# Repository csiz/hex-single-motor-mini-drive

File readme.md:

Hex Mini FOC driver
===================

Brushless motor driver for mini gear motors and servos. This driver focuses on fine force control
using field oriented control (FOC). The motor can be commanded to move to track position, 
velocity, and/or force. The driver will maintain the current wave exactly 90 degrees out
of phase to the EMF wave for maximum efficieny. Position is tracked via hall sensors, EMF
feedback and I2C rotary sensors.

Electrical ranges: 
- Maximum motor voltage: 28V
- Maximum current: 5A
- Minimum motor voltage: 6V
- Nominal I2C voltage: 3.3V

This project has 4 main components, for details look at the `readme.md` files in each directory:
* A brushless motor simulator and motor principles explainer; under `motor-sim`.
* The driver PCB schematic and manufacturing files; under `circuits`.
* Custom driver firmware with Kalman filter position tracking and FOC driving logic; under `driver-code`.
* Driver control and monitoring webapp; also under `motor-sim`, the page titled `motor-monitor.md`.
* The interface spec and autogenerated serialization code under `interface`; because of this we
must use the `npm update --install-links` command when updating dependencies for `motor-sim`.
(TODO: this section needs updating to include the master circuit and master code and versioning and media and circuit libraries layout)

Screenshots
-----------

Motor monitor should look like this when connected to a motor: 

The motor sim, with GPU rendered soundwaves should look like this: 

Circuit Dev Log
---------------

Lessons learnt for driver code v0.4
-----------------------------------

[ ] VREF must be independent of the reference to the amplifier; and actually well insulated. The v0.2 and v0.3 are too noisy because of this I suspect.
[ ] Let's go back to USB with 5V and separate VCC power connector! Also allows us to drop the on-board buck converter and save space. Bonus for easy to
control from a computer/phone with any USB cable.

Tasks for v0.3
--------------

[v] Maybe switch to a oscillation damping gate resistor of 3ohm. The AO4266E switching parameter uses 
Rgen = 3ohm, I think this is their recommended gate resistance. Switched to 4.7ohm, closest basic resistor.

[v] Aaaargh!!! BOOT0 pin needs a pulldown resistor on the STM32G4!
[x] VREF+ should be tied to VDDA... VREF+ now has the capacitance required and drives the amplifier refrence too.

[v] Think about connectors better. We should either drop or double down on USB-C. It would be very user friendly and the power delivery 
allows us to pick the 9-24V we need, but might be cumbersombe to control 24 devices. The SPI bus with slim connectors let's us keep it 
tight and in-house. Would we want a cheap single-sided board with USB-C and also a compact double sided assembly without USB at all.
... Let's go for double sided compact without USB, with the better stm32g4 with 5 opamps (so we can also ditch the opamp).
[v] USB-C footprint was correct with the cutouts. What we have now is incorrect!

[v] Need master circuit.
[v] Need flexi rotation I2C sensors.
[v] Via diameter was too small, should be at least 0.2/0.45

Need to implement in v0.2
-------------------------

Features of current version:
[v] Measure power line voltage.
[x] Re-pick voltage boost capacitor and resistor pair (using P FETS).
[v] Re-pick gate oscillation damping resistor for the inputs to the power MOSFET.
[v] Crystal oscilator and pick matching caps.
[v] Power regulator.
[v] USB-C connector maybe?
[v] Debugging connection with the trace line.
[v] 4 half bridge outputs
[v] 4 voltage inputs for the 4 outputs
[v] 1 voltage input for VCC
[v] 2 (preferably 4) current inputs from the 4 outputs; I chose 4.
[x] maybe 1 current input for total current. It would leave us with a floating ground which is iffy.
[v] SPI connection to main board. Not ~I2C~, it's too slow and consumes too much current. SPI will need
a chip select pin, but allows for parallel devices. SPI has hardware CRC calculation, seems useful.
[v] Spare I2C connection for the magnetic sensors.
[v] Status LED.

Lessons from previous version:
[x] Measure gate turn on characteristics of existing circuit...
[x] Maybe switch to a oscillation damping gate resistor of 3ohm. The AO4266E switching parameter uses 
Rgen = 3ohm, I think this is their recommended gate resistance.
[x] Definitely need to think about daisy chaining these, maybe use a signal buffer/transciever with an enable pin,
and/or mosfet switch for the chip power on. I2C to master board is probably the best and easiest way.
[v] Oopsies I flipped the sign of the V phase current measurement lines.
[x] The boost gate should maybe be connected to the driver side of the shunt resistor. At the moment we're measuring current used to charge the high gate.
[x] There's a summing option for the current measurments. Try outputing U, V, U+V, U+V+W using the 4th spare output.
[v] ! Think carefully about the shunt resistor placement, there's big interference going on if we measure during high side. Timing it around ground as
common mode voltage seems to fix it. Is that the only way to measure all current going through the motor coils?
[v] ! Measure voltage of the motor coils!
[x] There's a conflict between i2c and timer 3 channel 2. Choose a different GPIO for the red LED.
	I2C1 and TIM3_CH2 remapped
	Description
	When the following conditions are met:
	• I2C1 and TIM3 are clocked.
	• I/O port pin PB5 is configured as an alternate function output
	there is a conflict between the TIM3_CH2 signal and the I2C1 SMBA signal (even if SMBA is not used).
	In these cases the I/O port pin PB5 is set to 1 by default if the I/O alternate function output is selected and I2C1 is
	clocked. TIM3_CH2 cannot be used in output mode.
	Workaround
	To avoid this conflict, TIM3_CH2 can only be used in input mode.

[x] Double sided board. Not just yet.
[x] Drop voltage regulator and rely on master board for 3.3V; filter it though. We just needed to look for better 
components, there are cheap and small options that work well for us.
[x] Look for thinner IDC connector, and definitely SMD version for easier routing, use of space behind connector.
[v] Add voltage probes for the phase connectors so we can measure voltage both during driving and open connections.
We need to measure driving voltage to make sure our MOSFETS are turned on and giving us the voltage we command!
[v] Use Kelvin sense resistors (or pad hack) for the current measurement to avoid the unknown solder resistance.
https://www.analog.com/media/en/analog-dialogue/volume-46/number-2/articles/optimize-high-current-sensing-accuracy.pdf
[v] Don't drop the hall sensors, yet!
[v] The big problem with our measurements occurs when we switch from continuous 0 output from the low mosfet to mixed
output with the high mosfet. Any amount of mixed output seems to add an offset to our current measurement. Might be
worth putting the current sense only on the low mosfet branch.
[x] Choose a different mosfet driver to lower the minimum voltage under 5V. The undervoltage protection must be there
for a reason. Anyway, we chose 6V and up.
[v] Make it work with steppers... Neat!

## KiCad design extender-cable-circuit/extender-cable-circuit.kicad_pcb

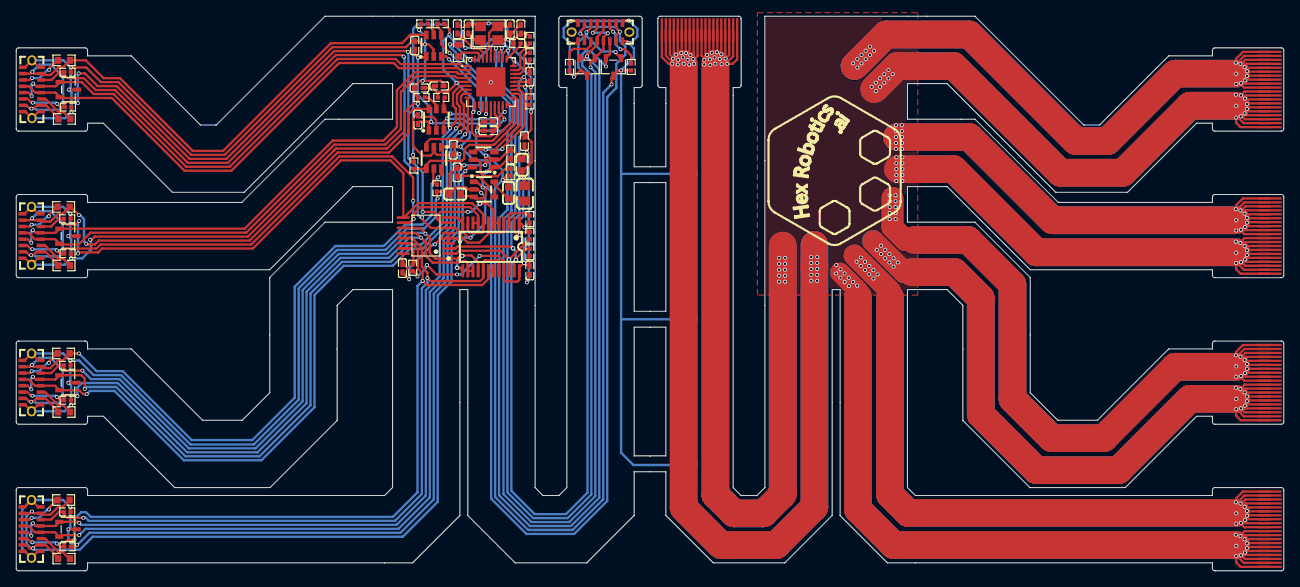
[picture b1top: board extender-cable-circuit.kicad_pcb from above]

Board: 2 copper layers, 160.0 x 70.0 mm, 80 parts (0 on the bottom side), 62 nets.

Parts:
C1, C2, C4, C5, C6, C7, C10, C11, C13, C14, C15, C16, C17, C18: 100nF; C0402
C8, C12, C20: 1uF; C0603
C19: 10nF; C0402
C72, C74: 15pF; C0402
D8, D10, D12, D14, D16, D18: SOT-23-3_L3.0-W1.7-P0.95-LS2.9-BR
FPC0, FPC1, FPC2, FPC3, FPC4: FPC-20P-P0.50-Pattern
L2: 10uH; L0805
R1, R2, R3, R4, R5, R8, R9: 10kΩ; R0402
R6, R7: 5.1kΩ; R0402
R17, R18, R19, R20, R76, R77, R78, R81: 56kΩ; R0603
R35, R55, R61, R66: 20kΩ; R0402
R54: 12kΩ; R0603
R79, R80, R82, R83: 100kΩ; R0402
R96, R97, R98, R99, R103, R104, R105, R106: 1MΩ; R0402
U1: TQFN-36_L6.0-W6.0-P0.50-BL-EP3.7
U3: SOT-23-5_L3.0-W1.6-P0.95-LS2.8-BL
U7, U23, U26, U28: SOT-23-6_L2.9-W1.6-P0.95-LS2.8-BR
U9: TSSOP-24_L7.8-W4.4-P0.65-LS6.4-BL
U14: TSSOP-16_L5.0-W4.4-P0.65-LS6.4-BL
USB0, USB1, USB2, USB3, USB4: USB-C-SMD_TC-005
X3: 24MHz; CRYSTAL-SMD_4P-L3.2-W2.5-BL

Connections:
3V3: C1.2, C2.2, C5.2, C6.2, C7.2, C10.2, C12.2, C13.2, C14.2, L2.2, R1.1, R2.2, R3.2, R4.1, R5.1, R8.1, R79.1, R80.1, R82.1, R83.1, U1.5 (VDDA33), U1.10 (VDDA33), U1.15 (VDD33), U1.23 (VDD33), U1.27 (VBUS_DET), U1.29 (VDDA33), U1.36 (VDDA33), U9.2 (A1), U9.21 (A2), U9.24 (VCC), U14.16 (VDD)
/3V3-before-filter: C8.2, L2.1, U3.5 (OUT)
/CC1: R6.2, USB0.A5 (CC1)
/CC2: R7.2, USB0.B5 (CC2)
/CFG_SEL1: R9.2, U1.25 (HS_IND/CFG_SEL1)
/LDO-Bypass-Capacitor: C19.2, U3.4 (BYP)
/NRESET: R5.2, U1.26 (RESET_N)
/PLLFILT: C4.2, U1.34 (PLLFILT)
/RBIAS: R54.1, U1.35 (RBIAS)
/XTAL1: C72.1, U1.33 (XTALIN/CLKIN), X3.1 (OSC1)
/XTAL2: C74.2, U1.32 (XTALOUT), X3.3 (OSC2)
/servo-usb-connector1/CC1x: R77.1, USB2.A5 (CC1)
/servo-usb-connector1/CC2x: R18.1, USB2.B5 (CC2)
/servo-usb-connector1/ILIMx: R55.2, U23.5 (ILIM)
/servo-usb-connector1/VBUSx: R18.2, R77.2, U23.6 (OUT), USB2.A4 (VBUS), USB2.A9 (VBUS), USB2.B4 (VBUS), USB2.B9 (VBUS)
/servo-usb-connector2/CC1x: R78.1, USB3.A5 (CC1)
/servo-usb-connector2/CC2x: R19.1, USB3.B5 (CC2)
/servo-usb-connector2/ILIMx: R61.2, U26.5 (ILIM)
/servo-usb-connector2/VBUSx: R19.2, R78.2, U26.6 (OUT), USB3.A4 (VBUS), USB3.A9 (VBUS), USB3.B4 (VBUS), USB3.B9 (VBUS)
/servo-usb-connector3/CC1x: R81.1, USB4.A5 (CC1)
/servo-usb-connector3/CC2x: R20.1, USB4.B5 (CC2)
/servo-usb-connector3/ILIMx: R66.2, U28.5 (ILIM)
/servo-usb-connector3/VBUSx: R20.2, R81.2, U28.6 (OUT), USB4.A4 (VBUS), USB4.A9 (VBUS), USB4.B4 (VBUS), USB4.B9 (VBUS)
/servo-usb-connector/CC1x: R76.1, USB1.A5 (CC1)
/servo-usb-connector/CC2x: R17.1, USB1.B5 (CC2)
/servo-usb-connector/ILIMx: R35.2, U7.5 (ILIM)
/servo-usb-connector/VBUSx: R17.2, R76.2, U7.6 (OUT), USB1.A4 (VBUS), USB1.A9 (VBUS), USB1.B4 (VBUS), USB1.B9 (VBUS)
GND: C1.1, C2.1, C4.1, C5.1, C6.1, C7.1, C8.1, C10.1, C11.1, C12.1, C13.1, C14.1, C15.1, C16.1, C17.1, C18.1, C19.1, C20.1, C72.2, C74.1, D8.3 (K), D10.3 (K), D12.3 (K), D14.3 (K), D16.3 (K), D18.3 (K), FPC0.1, FPC0.2, FPC0.3, FPC0.4, FPC0.5, FPC0.6, FPC0.7, FPC0.8, FPC0.9, FPC0.10, FPC1.1, FPC1.2, FPC1.3, FPC1.4, FPC1.5, FPC1.6, FPC1.7, FPC1.8, FPC1.9, FPC1.10, FPC2.1, FPC2.2, FPC2.3, FPC2.4, FPC2.5, FPC2.6, FPC2.7, FPC2.8, FPC2.9, FPC2.10, FPC3.1, FPC3.2, FPC3.3, FPC3.4, FPC3.5, FPC3.6, FPC3.7, FPC3.8, FPC3.9, FPC3.10, FPC4.1, FPC4.2, FPC4.3, FPC4.4, FPC4.5, FPC4.6, FPC4.7, FPC4.8, FPC4.9, FPC4.10, R6.1, R7.1, R9.1, R35.1, R54.2, R55.1, R61.1, R66.1, R96.1, R97.1, R98.1, R99.1, R103.1, R104.1, R105.1, R106.1, U1.37 (EP), U3.2 (GND), U7.2 (GND), U9.1 (A0), U9.12 (GND), U14.3 (A0), U14.4 (A1), U14.5 (A2), U14.8 (VSS), U23.2 (GND), U26.2 (GND), U28.2 (GND), USB0.A1 (GND), USB0.A12 (GND), USB0.B1 (GND), USB0.B12 (GND), USB1.1 (EH), USB1.2 (EH), USB1.A1 (GND), USB1.A12 (GND), USB1.B1 (GND), USB1.B12 (GND), USB2.1 (EH), USB2.2 (EH), USB2.A1 (GND), USB2.A12 (GND), USB2.B1 (GND), USB2.B12 (GND), USB3.1 (EH), USB3.2 (EH), USB3.A1 (GND), USB3.A12 (GND), USB3.B1 (GND), USB3.B12 (GND), USB4.1 (EH), USB4.2 (EH), USB4.A1 (GND), USB4.A12 (GND), USB4.B1 (GND), USB4.B12 (GND), X3.2 (GND), X3.4 (GND)
I2C_SCL: D10.2 (A1), R2.1, U1.24 (SCL/SMBCLK/CFG_SEL0), U9.22 (SCL), U14.1 (SCL), USB0.A8 (SUB1)
I2C_SDA: D10.1 (A1), R3.1, U1.22 (SDA/SMBBATA/NON_REM1), U9.23 (SDA), U14.2 (SDA), USB0.B8 (SUB2)
IN_USB_D+: D8.2 (A1), U1.31 (USBDP_UP), USB0.A6 (DP1), USB0.B6 (DP2)
IN_USB_D-: D8.1 (A1), U1.30 (USBDM_UP), USB0.A7 (DN1), USB0.B7 (DN2)
unnamed: C11.2, U1.14 (CRFILT)
unnamed: R8.2, U1.28 (SUSP_IND/LOCAL_PWR/NON_REM0)
unnamed: R1.2, U9.3 (RESET#)
unnamed: R4.2, U14.15 (RESET#)
PRTPWR1: U1.12 (PRTPWR1/BC_EN1), U7.3 (EN)
PRTPWR2: U1.16 (PRTPWR2/BC_EN2), U23.3 (EN)
PRTPWR3: U1.18 (PRTPWR3/BC_EN3), U26.3 (EN)
PRTPWR4: U1.20 (PRTPWR4/BC_EN4), U28.3 (EN)
SERVO1_BOOT0: R96.2, U9.4 (SD0), U9.7 (SC1), U14.6 (IO0), USB1.A8 (SUB1)
SERVO1_NRST: R103.2, U9.5 (SC0), U9.6 (SD1), U14.7 (IO1), USB1.B8 (SUB2)
SERVO2_BOOT0: R97.2, U9.8 (SD2), U9.11 (SC3), U14.9 (IO2), USB2.A8 (SUB1)
SERVO2_NRST: R104.2, U9.9 (SC2), U9.10 (SD3), U14.10 (IO3), USB2.B8 (SUB2)
SERVO3_BOOT0: R98.2, U9.13 (SD4), U9.16 (SC5), U14.11 (IO4), USB3.A8 (SUB1)
SERVO3_NRST: R105.2, U9.14 (SC4), U9.15 (SD5), U14.12 (IO5), USB3.B8 (SUB2)
SERVO4_BOOT0: R99.2, U9.17 (SD6), U9.20 (SC7), U14.13 (IO6), USB4.A8 (SUB1)
SERVO4_NRST: R106.2, U9.18 (SC6), U9.19 (SD7), U14.14 (IO7), USB4.B8 (SUB2)
USBDN1_D+: D12.2 (A1), U1.2 (USBDP_DN1/PRT_DIS_P1), USB1.A6 (DP1), USB1.B6 (DP2)
USBDN1_D-: D12.1 (A1), U1.1 (USBDM_DN1/PRT_DIS_M1), USB1.A7 (DN1), USB1.B7 (DN2)
USBDN2_D+: D14.2 (A1), U1.4 (USBDP_DN2/PRT_DIS_P2), USB2.A6 (DP1), USB2.B6 (DP2)
USBDN2_D-: D14.1 (A1), U1.3 (USBDM_DN2/PRT_DIS_M2), USB2.A7 (DN1), USB2.B7 (DN2)
USBDN3_D+: D16.2 (A1), U1.7 (USBDP_DN3/PRT_DIS_P3), USB3.A6 (DP1), USB3.B6 (DP2)
USBDN3_D-: D16.1 (A1), U1.6 (USBDM_DN3/PRT_DIS_M3), USB3.A7 (DN1), USB3.B7 (DN2)
USBDN4_D+: D18.2 (A1), U1.9 (USBDP_DN4/PRT_DIS_P4), USB4.A6 (DP1), USB4.B6 (DP2)
USBDN4_D-: D18.1 (A1), U1.8 (USBDM_DN4/PRT_DIS_M4), USB4.A7 (DN1), USB4.B7 (DN2)
VBUS: C15.2, C16.2, C17.2, C18.2, C20.2, U3.1 (IN), U3.3 (EN), U7.1 (IN), U23.1 (IN), U26.1 (IN), U28.1 (IN), USB0.A4 (VBUS), USB0.A9 (VBUS), USB0.B4 (VBUS), USB0.B9 (VBUS)
VCC: FPC0.11, FPC0.12, FPC0.13, FPC0.14, FPC0.15, FPC0.16, FPC0.17, FPC0.18, FPC0.19, FPC0.20, FPC1.11, FPC1.12, FPC1.13, FPC1.14, FPC1.15, FPC1.16, FPC1.17, FPC1.18, FPC1.19, FPC1.20, FPC2.11, FPC2.12, FPC2.13, FPC2.14, FPC2.15, FPC2.16, FPC2.17, FPC2.18, FPC2.19, FPC2.20, FPC3.11, FPC3.12, FPC3.13, FPC3.14, FPC3.15, FPC3.16, FPC3.17, FPC3.18, FPC3.19, FPC3.20, FPC4.11, FPC4.12, FPC4.13, FPC4.14, FPC4.15, FPC4.16, FPC4.17, FPC4.18, FPC4.19, FPC4.20
nOCS1: R79.2, U1.13 (OCS_N1), U7.4 (/FAULT)
nOCS2: R80.2, U1.17 (OCS_N2), U23.4 (/FAULT)
nOCS3: R82.2, U1.19 (OCS_N3), U26.4 (/FAULT)
nOCS4: R83.2, U1.21 (OCS_N4), U28.4 (/FAULT)

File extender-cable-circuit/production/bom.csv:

Designator,Footprint,Quantity,Value,LCSC Part #
"C1, C10, C11, C13, C14, C15, C16, C17, C18, C2, C4, C5, C6, C7",C0402,14,100nF,C60474
"C12, C20, C8",C0603,3,1uF,C15849
C19,C0402,1,10nF,C15195
"C72, C74",C0402,2,15pF,C1548
"D10, D12, D14, D16, D18, D8",SOT-23-3_L3.0-W1.7-P0.95-LS2.9-BR,6,~,C32677
L2,L0805,1,10uH,C1046
"R1, R2, R3, R4, R5, R8, R9",R0402,7,10kΩ,C25744
"R103, R104, R105, R106, R96, R97, R98, R99",R0402,8,1MΩ,C26083
"R17, R18, R19, R20, R76, R77, R78, R81",R0603,8,56kΩ,C23206
"R35, R55, R61, R66",R0402,4,20kΩ,C25765
R54,R0603,1,12kΩ,C22790
"R6, R7",R0402,2,5.1kΩ,C25905
"R79, R80, R82, R83",R0402,4,100kΩ,C25741
U1,TQFN-36_L6.0-W6.0-P0.50-BL-EP3.7,1,~,C58940
U14,TSSOP-16_L5.0-W4.4-P0.65-LS6.4-BL,1,~,C141380
"U23, U26, U28, U7",SOT-23-6_L2.9-W1.6-P0.95-LS2.8-BR,4,~,C55266
U3,SOT-23-5_L3.0-W1.6-P0.95-LS2.8-BL,1,~,C2969807
U9,TSSOP-24_L7.8-W4.4-P0.65-LS6.4-BL,1,~,C130026
"USB0, USB1, USB2, USB3, USB4",USB-C-SMD_TC-005,5,~,C6332285
X3,CRYSTAL-SMD_4P-L3.2-W2.5-BL,1,24MHz,C15643

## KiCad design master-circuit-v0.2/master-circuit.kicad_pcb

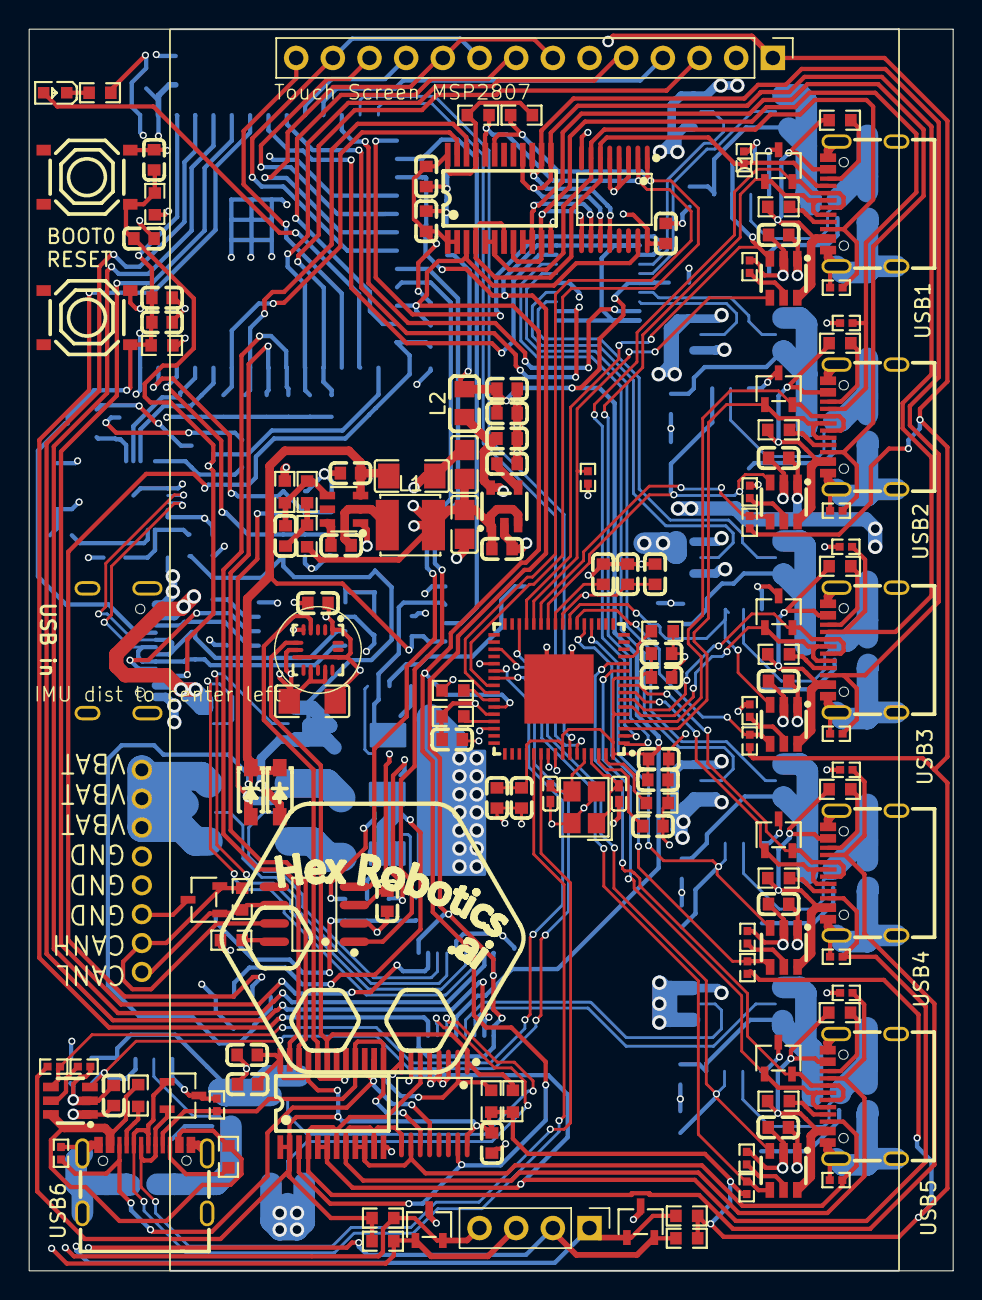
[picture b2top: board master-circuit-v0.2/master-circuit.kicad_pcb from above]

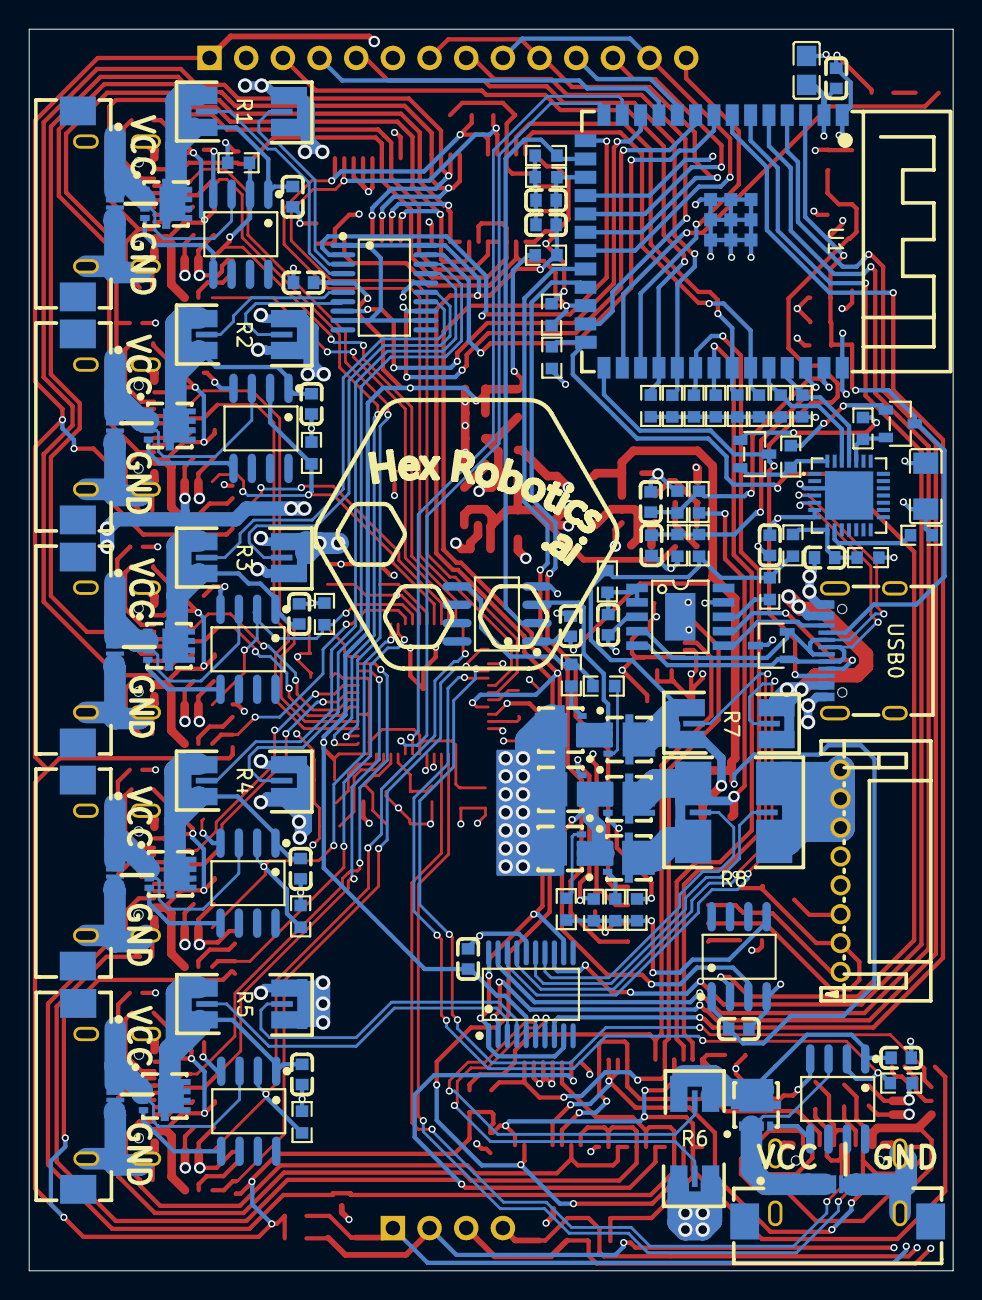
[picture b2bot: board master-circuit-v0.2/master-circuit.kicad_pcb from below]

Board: 4 copper layers, 64.0 x 86.0 mm, 238 parts (100 on the bottom side), 184 nets.

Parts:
C1, C8, C12, C15, C18, C20, C25, C26, C27, C28, C29, C33, C35, C40, C51, C52, C53, C54, C55, C56, C57, C58, C59, C63, C65, C71, C84, C85: 1uF; C0603
C2, C4, C5, C7, C13, C16, C22, C30, C31, C34, C38, C39, C42, C43, C44, C45, C60, C61, C62, C66, C67, C68, C70: 100nF; C0603
C3, C23, C24: 22uF; C0805
C6: 100pF; C0603
C9: 10nF; C0603
C10, C11: 1nF; C0603
C17, C21, C32: 10uF; C1206
C64, C69: 15pF; C0402
D1, D2, D4, D5, D6, D7, D8, D9, D10, D11: SOT-23-3_L3.0-W1.7-P0.95-LS2.9-BR
D12, D14: SOD-123_L2.7-W1.6-LS3.7-RD-1
FPC1, FPC2, FPC3, FPC4, FPC5, FPC6: FPC-SMD_20P-P0.50_XUNPU_FPC-05F-20PH20
L1: 15uH; IND-SMD_L4.0-W4.0
L2: 10uH; L0805
LED1: LED0603-RD
Q8, Q12, Q14, Q16, Q18, Q20, Q21, Q22, Q23, Q24, Q25, Q26: WDFN-5_L3.1-W3.1-P0.65-BL_1
Q9, Q10: SOT-23-3_L2.9-W1.3-P1.90-LS2.4-BR
R1, R2, R3, R4, R5, R6, R7: 5mΩ; R2512 Shunt with Kelvin connections
R8: 1mΩ; R2725 Shunt with Kelvin connections
R9, R11, R12, R14, R15, R17, R18, R21, R22, R24, R25, R26, R27, R29, R30, R31, R32, R33, R34, R37, R38, R42, R43, R44, R47, R51, R52, R53, R58, R60, R64, R72, R73, R74, R78, R95, R102, R109: 10kΩ; R0603
R10: 49.9Ω; R0603
R13, R28, R46, R59, R65, R71, R76, R85, R86, R87, R88, R89: 56kΩ; R0603
R16: 120Ω; R0603
R23, R39: 1.5kΩ; R0603
R35, R55, R61, R66, R67, R70: 20kΩ; R0402
R40: 20kΩ; R0603
R41: 47kΩ; R0603
R45, R48, R56: 100kΩ; R0603
R50: 12kΩ; R0603
R62: 13kΩ; R0603
R68: 1kΩ; R0603
R77, R81, R90, R92, R93, R94: 4.7Ω; R0603
R79, R80, R82, R83, R84, R91: 100kΩ; R0402
R96, R97, R98, R99, R100, R101, R103, R104, R105, R106, R107, R108: 1MΩ; R0402
SW1, SW2: SW-SMD_4P-L5.1-W5.1-P3.70-LS6.5-TL_H1.5
U1: WIRELM-SMD_ESP32-S3-WROOM-1
U3: SOT-23-5_L3.0-W1.6-P0.95-LS2.8-BL
U4: SOT-23-6_L2.9-W1.6-P0.95-LS2.8-BL
U7, U23, U26, U28, U30, U32: SOT-23-6_L2.9-W1.6-P0.95-LS2.8-BR
U9, U13: TSSOP-24_L7.8-W4.4-P0.65-LS6.4-BL
U10: QFN-28_L5.0-W5.0-P0.50-TL-EP3.3
U11, U16: TSSOP-20_L6.5-W4.4-P0.65-LS6.4-BL
U14, U15: TSSOP-16_L5.0-W4.4-P0.65-LS6.4-BL
U17, U41, U43, U44, U45, U46, U47, U48, U49: SOIC-8_L4.9-W3.9-P1.27-LS6.0-BL
U18: LGA-16_L3.0-W3.0-P0.50-TL
U19: CONN-TH_S8B-PH-K-S-LF-SN
U24: QFN-64_L9.0-W9.0-P0.50-BL-EP4.8
U35: MSP2807 OLED with touchescreen and SD card
U42: ESSOP-10_L4.9-W3.9-P1.0-LS6.0-TL-EP
USB0, USB1, USB2, USB3, USB4, USB5, USB6: USB-C-SMD_TYPE-C16PIN
X2: 24MHz; CRYSTAL-SMD_4P-L3.2-W2.5-BL

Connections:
3V3: C2.2, C3.2, C8.2, C16.2, C17.2, C30.2, C31.2, C32.2, C42.2, C43.2, C44.2, C45.2, C59.2, C60.2, C68.2, C84.2, C85.2, L2.1, R9.2, R14.2, R15.2, R17.2, R18.2, R24.2, R25.2, R26.2, R27.2, R29.2, R32.2, R33.2, R34.2, R37.2, R39.1, R42.1, R51.2, R53.2, R58.2, R60.2, R64.2, R79.1, R80.1, R82.1, R83.1, R84.1, R91.1, U1.2 (3V3), U3.5 (OUT), U9.1 (A0), U9.2 (A1), U9.21 (A2), U9.24 (VCC), U10.6 (VDD), U10.7 (VREGIN), U13.1 (A0), U13.2 (A1), U13.21 (A2), U13.24 (VCC), U14.16 (VDD), U15.16 (VDD), U17.3 (VCC), U18.1 (VDD_IO), U18.8 (CS), U18.14 (VDD), U24.24 (VDD33CR), U24.37 (OCS7_N), U24.44 (VBUS_DET), U24.46 (VDD33), U35.1 (VCC)
3V3A: C12.2, C13.2, C38.2, C39.2, C61.2, C62.2, C66.2, C67.2, C70.2, C71.2, L2.2, R21.2, U11.5 (VS), U16.5 (VS), U24.5 (VDDA33), U24.10 (VDDA33), U24.52 (VDDA33), U24.57 (VDDA33), U24.64 (VDD33PLL)
5V: C15.2, C20.2, C23.2, C24.2, C26.2, C27.2, C28.2, C33.2, C40.2, L1.2, R10.2, U3.1 (IN), U3.3 (EN), U7.1 (IN), U23.1 (IN), U26.1 (IN), U28.1 (IN), U30.1 (IN), U32.1 (IN)
+Probe-1: R1.4 (Probe-2), U11.3 (IN±1)
+Probe-2: R2.4 (Probe-2), U11.7 (IN±2)
+Probe-3: R3.4 (Probe-2), U11.15 (IN+3)
+Probe-4: R4.4 (Probe-2), U11.18 (IN±4)
+Probe-5: R5.4 (Probe-2), U16.4 (IN+1)
+Probe-6: R6.4 (Probe-2), U16.7 (IN±2)
+Probe-7: R7.4 (Probe-2), U16.17 (IN+4)
+Probe-8: R8.4 (Probe-2), U16.14 (IN±3)
-Probe-1: R1.3 (Probe-1), U11.4 (IN+1)
-Probe-2: R2.3 (Probe-1), U11.6 (IN+2)
-Probe-3: R3.3 (Probe-1), U11.14 (IN±3)
-Probe-4: R4.3 (Probe-1), U11.17 (IN+4)
-Probe-5: R5.3 (Probe-1), U16.3 (IN±1)
-Probe-6: R6.3 (Probe-1), U16.6 (IN+2)
-Probe-7: R7.3 (Probe-1), U16.18 (IN±4)
-Probe-8: R8.3 (Probe-1), U16.15 (IN+3)
/Buck-Bootstrap-Capacitor: C7.1, U4.6 (BOOT)
/Buck-Output-SW: C7.2, L1.1, U4.2 (SW)
/Buck-Probe-Point: C6.2, R10.1, R56.2
/CAN-RS-SLOPE_CONTROL: R31.2, U17.8 (RS)
/CFG_SEL1: R52.2, U24.42 (HS_IND/CFG_SEL1)
/CFG_SEL2: R30.2, U24.13 (CFG_SEL2)
/DTR-GATE: Q9.1 (B), R43.1
/Gate1-vbattery: Q18.4 (G), R90.2
/Gate1-vbus: Q14.4 (G), R81.2
/Gate2-vbattery: Q20.4 (G), R92.2
/Gate2-vbus: Q16.4 (G), R77.2
/Gate3-vbattery: Q21.4 (G), R93.2
/Gate4-vbattery: Q22.4 (G), R94.2
/LDO-Bypass-Capacitor: C9.2, U3.4 (BYP)
/PD-VBUS-DETECT: R72.2, U42.8 (VBUS)
/PD-VDD: C29.2, R68.2, U42.1 (VDD), U42.2 (CFG2)
/RBIAS: R50.1, U24.63 (RBIAS)
/RTS-GATE: Q10.1 (B), R44.1
/Source-vbattery: Q18.1 (S), Q18.2 (S), Q18.3 (S), Q20.1 (S), Q20.2 (S), Q20.3 (S), Q21.1 (S), Q21.2 (S), Q21.3 (S), Q22.1 (S), Q22.2 (S), Q22.3 (S), U47.3 (Source)
/Source-vbus: Q14.1 (S), Q14.2 (S), Q14.3 (S), Q16.1 (S), Q16.2 (S), Q16.3 (S), U46.3 (Source)
/VBATTERY_PINS: R8.1 (Shunt-1), U19.6, U19.7, U19.8
/VDD18PLL: C65.2, U24.62 (VDD18PLL)
/XTAL1: C64.1, U24.61 (XTAL1/CLKIN), X2.1 (OSC1)
/XTAL2: C69.2, U24.60 (XTAL2), X2.3 (OSC2)
/servo-usb-connector1/CC1x: R28.2, USB2.A5 (CC1)
/servo-usb-connector1/CC2x: R85.1, USB2.B5 (CC2)
/servo-usb-connector1/ILIMx: R55.2, U23.5 (ILIM)
/servo-usb-connector1/VBUSx: R28.1, R85.2, U23.6 (OUT), USB2.A4B9 (VBUS), USB2.B4A9 (VBUS)
/servo-usb-connector1/VCCx: FPC2.1, FPC2.2, FPC2.3, FPC2.4, FPC2.5, FPC2.6, FPC2.7, FPC2.8, FPC2.9, FPC2.10, Q12.1 (S), Q12.2 (S), Q12.3 (S), U43.3 (Source)
/servo-usb-connector1/VCCx-probe: C52.2, Q12.5 (D), R2.1 (Shunt-1), U43.1 (V+)
/servo-usb-connector2/CC1x: R46.2, USB3.A5 (CC1)
/servo-usb-connector2/CC2x: R86.1, USB3.B5 (CC2)
/servo-usb-connector2/ILIMx: R61.2, U26.5 (ILIM)
/servo-usb-connector2/VBUSx: R46.1, R86.2, U26.6 (OUT), USB3.A4B9 (VBUS), USB3.B4A9 (VBUS)
/servo-usb-connector2/VCCx: FPC3.1, FPC3.2, FPC3.3, FPC3.4, FPC3.5, FPC3.6, FPC3.7, FPC3.8, FPC3.9, FPC3.10, Q23.1 (S), Q23.2 (S), Q23.3 (S), U44.3 (Source)
/servo-usb-connector2/VCCx-probe: C53.2, Q23.5 (D), R3.1 (Shunt-1), U44.1 (V+)
/servo-usb-connector3/CC1x: R59.2, USB4.A5 (CC1)
/servo-usb-connector3/CC2x: R87.1, USB4.B5 (CC2)
/servo-usb-connector3/ILIMx: R66.2, U28.5 (ILIM)
/servo-usb-connector3/VBUSx: R59.1, R87.2, U28.6 (OUT), USB4.A4B9 (VBUS), USB4.B4A9 (VBUS)
/servo-usb-connector3/VCCx: FPC4.1, FPC4.2, FPC4.3, FPC4.4, FPC4.5, FPC4.6, FPC4.7, FPC4.8, FPC4.9, FPC4.10, Q24.1 (S), Q24.2 (S), Q24.3 (S), U45.3 (Source)
/servo-usb-connector3/VCCx-probe: C54.2, Q24.5 (D), R4.1 (Shunt-1), U45.1 (V+)
/servo-usb-connector4/CC1x: R65.2, USB5.A5 (CC1)
/servo-usb-connector4/CC2x: R88.1, USB5.B5 (CC2)
/servo-usb-connector4/ILIMx: R67.2, U30.5 (ILIM)
/servo-usb-connector4/VBUSx: R65.1, R88.2, U30.6 (OUT), USB5.A4B9 (VBUS), USB5.B4A9 (VBUS)
/servo-usb-connector4/VCCx: FPC5.1, FPC5.2, FPC5.3, FPC5.4, FPC5.5, FPC5.6, FPC5.7, FPC5.8, FPC5.9, FPC5.10, Q25.1 (S), Q25.2 (S), Q25.3 (S), U48.3 (Source)
/servo-usb-connector4/VCCx-probe: C57.2, Q25.5 (D), R5.1 (Shunt-1), U48.1 (V+)
/servo-usb-connector5/CC1x: R71.2, USB6.A5 (CC1)
/servo-usb-connector5/CC2x: R89.1, USB6.B5 (CC2)
/servo-usb-connector5/ILIMx: R70.2, U32.5 (ILIM)
/servo-usb-connector5/VBUSx: R71.1, R89.2, U32.6 (OUT), USB6.A4B9 (VBUS), USB6.B4A9 (VBUS)
/servo-usb-connector5/VCCx: FPC6.1, FPC6.2, FPC6.3, FPC6.4, FPC6.5, FPC6.6, FPC6.7, FPC6.8, FPC6.9, FPC6.10, Q26.1 (S), Q26.2 (S), Q26.3 (S), U49.3 (Source)
/servo-usb-connector5/VCCx-probe: C58.2, Q26.5 (D), R6.1 (Shunt-1), U49.1 (V+)
/servo-usb-connector/CC1x: R13.2, USB1.A5 (CC1)
/servo-usb-connector/CC2x: R76.1, USB1.B5 (CC2)
/servo-usb-connector/ILIMx: R35.2, U7.5 (ILIM)
/servo-usb-connector/VBUSx: R13.1, R76.2, U7.6 (OUT), USB1.A4B9 (VBUS), USB1.B4A9 (VBUS)
/servo-usb-connector/VCCx: FPC1.1, FPC1.2, FPC1.3, FPC1.4, FPC1.5, FPC1.6, FPC1.7, FPC1.8, FPC1.9, FPC1.10, Q8.1 (S), Q8.2 (S), Q8.3 (S), U41.3 (Source)
/servo-usb-connector/VCCx-probe: C51.2, Q8.5 (D), R1.1 (Shunt-1), U41.1 (V+)
BATTERY_CURRENT: U1.6 (IO6), U16.13 (OUT3)
BATTERY_VOLTAGE: C11.2, R38.2, R48.1, U1.39 (IO1)
BOOT0: C4.2, C25.2, Q10.3 (C), R42.2, SW1.1 (A), U1.27 (IO0), USB0.B8 (SBU2)
Buck-FB: C6.1, R56.1, R62.2, U4.4 (FB)
CANH: D7.2 (A1), R16.2, U17.7 (CANH), U19.2
CANL: D7.1 (A1), R16.1, U17.6 (CANL), U19.1
CAN_RX: U1.23 (IO21), U17.4 (R)
CAN_TX: U1.22 (IO14), U17.1 (D)
CC1: U42.7 (CC1), USB0.A5 (CC1)
CC2: U42.6 (CC2), USB0.B5 (CC2)
CONNECT_BATTERY: R11.2, U1.26 (IO45), U47.2 (Input)
CONNECT_VBUS: R12.2, U1.16 (IO46), U46.2 (Input)
DTR: Q10.2 (E), R43.2, U10.28 (DTR)
ENABLE-ESP32: C1.2, C5.2, Q9.3 (C), R37.1, SW2.1 (A), U1.3 (EN), USB0.A8 (SBU1)
FSPICLK/SPI2_CLK: D4.2 (A1), R14.1, U1.20 (IO12), U35.7 (SCK), U35.10 (T_CLK), U35.18 (SD_SCK)
FSPICS0/MEMORY_CS: D6.1 (A1), R9.1, U1.18 (IO10), U35.15 (SD_CS)
FSPID/SPI2_MOSI: D6.2 (A1), R34.1, U1.19 (IO11), U35.6 (SDI/MOSI), U35.12 (T_DIN), U35.16 (SD_MOSI)
FSPIQ/SPI2_MISO: D4.1 (A1), R15.1, U1.21 (IO13), U35.9 (SD0/MISO), U35.13 (T_DO), U35.17 (SD_MISO)
GND: C1.1, C2.1, C3.1, C4.1, C5.1, C8.1, C9.1, C10.1, C11.1, C12.1, C13.1, C15.1, C16.1, C17.1, C18.2, C20.1, C21.1, C22.1, C23.1, C24.1, C25.1, C26.1, C27.1, C28.1, C29.1, C30.1, C31.1, C32.1, C33.1, C34.1, C35.1, C38.1, C39.1, C40.1, C42.1, C43.1, C44.1, C45.1, C51.1, C52.1, C53.1, C54.1, C55.1, C56.1, C57.1, C58.1, C59.1, C60.1, C61.1, C62.1, C63.1, C64.2, C65.1, C66.1, C67.1, C68.1, C69.1, C70.1, C71.1, C84.1, C85.1, D1.3 (K), D2.3 (K), D4.3 (K), D5.3 (K), D6.3 (K), D7.3 (K), D8.3 (K), D9.3 (K), D10.3 (K), D11.3 (K), FPC1.11, FPC1.12, FPC1.13, FPC1.14, FPC1.15, FPC1.16, FPC1.17, FPC1.18, FPC1.19, FPC1.20, FPC2.11, FPC2.12, FPC2.13, FPC2.14, FPC2.15, FPC2.16, FPC2.17, FPC2.18, FPC2.19, FPC2.20, FPC3.11, FPC3.12, FPC3.13, FPC3.14, FPC3.15, FPC3.16, FPC3.17, FPC3.18, FPC3.19, FPC3.20, FPC4.11, FPC4.12, FPC4.13, FPC4.14, FPC4.15, FPC4.16, FPC4.17, FPC4.18, FPC4.19, FPC4.20, FPC5.11, FPC5.12, FPC5.13, FPC5.14, FPC5.15, FPC5.16, FPC5.17, FPC5.18, FPC5.19, FPC5.20, FPC6.11, FPC6.12, FPC6.13, FPC6.14, FPC6.15, FPC6.16, FPC6.17, FPC6.18, FPC6.19, FPC6.20, R11.1, R12.1, R22.1, R23.2, R30.1, R31.1, R35.1, R38.1, R41.2, R47.1, R50.2, R52.1, R55.1, R61.1, R62.1, R66.1, R67.1, R70.1, R73.1, R74.1, R78.1, R95.1, R96.1, R97.1, R98.1, R99.1, R100.1, R101.1, R102.1, R103.1, R104.1, R105.1, R106.1, R107.1, R108.1, R109.1, SW1.3 (C), SW2.3 (C), U1.1 (GND), U1.40 (GND), U1.41 (GND), U3.2 (GND), U4.1 (GND), U7.2 (GND), U9.12 (GND), U10.3 (GND), U10.29 (EP), U11.16 (GND), U13.12 (GND), U14.3 (A0), U14.4 (A1), U14.5 (A2), U14.8 (VSS), U15.3 (A0), U15.4 (A1), U15.5 (A2), U15.8 (VSS), U16.16 (GND), U17.2 (GND), U18.5 (GND), U18.7 (SDO/SA0), U18.10 (RES), U18.12 (GND), U19.3, U19.4, U19.5, U23.2 (GND), U24.55 (USBDN7_DM/PRT_DIS_M7), U24.56 (USBDN7_DP/PRT_DIS_P7), U24.65 (EP), U26.2 (GND), U28.2 (GND), U30.2 (GND), U32.2 (GND), U35.2 (GND), U41.4 (GND), U42.3 (CFG3), U42.9 (CFG1), U42.11 (GND), U43.4 (GND), U44.4 (GND), U45.4 (GND), U46.4 (GND), U47.4 (GND), U48.4 (GND), U49.4 (GND), USB0.A1B12 (GND), USB0.B1A12 (GND), USB1.1 (SHELL), USB1.2 (SHELL), USB1.3 (SHELL), USB1.4 (SHELL), USB1.A1B12 (GND), USB1.B1A12 (GND), USB2.1 (SHELL), USB2.2 (SHELL), USB2.3 (SHELL), USB2.4 (SHELL), USB2.A1B12 (GND), USB2.B1A12 (GND), USB3.1 (SHELL), USB3.2 (SHELL), USB3.3 (SHELL), USB3.4 (SHELL), USB3.A1B12 (GND), USB3.B1A12 (GND), USB4.1 (SHELL), USB4.2 (SHELL), USB4.3 (SHELL), USB4.4 (SHELL), USB4.A1B12 (GND), USB4.B1A12 (GND), USB5.1 (SHELL), USB5.2 (SHELL), USB5.3 (SHELL), USB5.4 (SHELL), USB5.A1B12 (GND), USB5.B1A12 (GND), USB6.1 (SHELL), USB6.2 (SHELL), USB6.3 (SHELL), USB6.4 (SHELL), USB6.A1B12 (GND), USB6.B1A12 (GND), X2.2 (GND), X2.4 (GND)
GUEST_USB_D+: D8.2 (A1), U10.4 (D+), U42.4 (DP), USB0.A6 (DP1), USB0.B6 (DP2)
GUEST_USB_D-: D8.1 (A1), U10.5 (D-), U42.5 (DM), USB0.A7 (DN1), USB0.B7 (DN2)
I2C1_INTERNAL_SCL: R53.1, U9.19 (SD7), U14.1 (SCL), U24.40 (SDA/SMBDATA/NON_REM1)
I2C1_INTERNAL_SDA: R58.1, U9.20 (SC7), U14.2 (SDA), U24.41 (SCL/SMBCLK/CFG_SEL0)
I2C1_SCL: R24.1, U1.34 (IO41), U9.22 (SCL)
I2C1_SDA: R25.1, U1.35 (IO42), U9.23 (SDA)
I2C2_INTERNAL_SCL: R60.1, U13.19 (SD7), U15.1 (SCL), U18.6 (SDA/SDI/SDO)
I2C2_INTERNAL_SDA: R64.1, U13.20 (SC7), U15.2 (SDA), U18.4 (SCL/SPC)
I2C2_SCL: R18.1, U1.33 (IO40), U13.22 (SCL)
I2C2_SDA: R17.1, U1.32 (IO39), U13.23 (SDA)
INTERNAL_GUEST_USB_D+: U1.14 (IO20), U24.59 (USBUP_DP)
INTERNAL_GUEST_USB_D-: U1.13 (IO19), U24.58 (USBUP_DM)
NRESET_ALL_MULTIPLEXERS: R29.1, U1.24 (IO47), U9.3 (RESET#), U13.3 (RESET#), U14.15 (RESET#), U15.15 (RESET#), U24.43 (RESET_N)
unnamed: LED1.1 (K), R23.1
unnamed: Q8.4 (G), U41.5 (Gate)
unnamed: Q12.4 (G), U43.5 (Gate)
unnamed: Q23.4 (G), U44.5 (Gate)
unnamed: Q24.4 (G), U45.5 (Gate)
unnamed: Q25.4 (G), U48.5 (Gate)
unnamed: Q26.4 (G), U49.5 (Gate)
unnamed: R39.2, U10.9 (RSTb)
unnamed: C18.1, R40.2, R41.1, U10.8 (VBUS)
unnamed: R51.1, U24.45 (SUSP_IND/LOCAL_PWR/NON_REM0)
unnamed: C63.2, U24.25 (VDD18)
unnamed: R77.1, R81.1, U46.5 (Gate)
unnamed: R90.1, R92.1, R93.1, R94.1, U47.5 (Gate)
PRTPWR1: R73.2, U7.3 (EN), U24.29 (PRTPWR1), U41.2 (Input)
PRTPWR2: R74.2, U23.3 (EN), U24.26 (PRTPWR2), U43.2 (Input)
PRTPWR3: R78.2, U24.23 (PRTPWR3), U26.3 (EN), U44.2 (Input)
PRTPWR4: R95.2, U24.20 (PRTPWR4), U28.3 (EN), U45.2 (Input)
PRTPWR5: R102.2, U24.30 (PRTPWR5), U30.3 (EN), U48.2 (Input)
PRTPWR6: R109.2, U24.39 (PRTPWR6), U32.3 (EN), U49.2 (Input)
REFERENCE: C34.2, C35.2, R21.1, R22.2, U1.17 (IO9), U11.1 (REF1), U11.9 (REF2), U11.12 (REF3), U11.20 (REF4), U16.1 (REF1), U16.9 (REF2), U16.12 (REF3), U16.20 (REF4)
RTS: Q9.2 (E), R44.2, U10.24 (RTS)
RX: R32.1, U1.36 (RXD0), U10.26 (TXD)
SCREEN_CS: R27.1, U1.30 (IO37), U35.3 (CS)
SCREEN_DC: R26.1, U1.31 (IO38), U35.5 (DC)
SCREEN_LED: U1.25 (IO48), U35.8 (LED)
SCREEN_RESET: U1.11 (IO18), U35.4 (RESET)
SERVO1_BOOT0: R103.2, U9.4 (SD0), U9.7 (SC1), U14.6 (IO0), USB1.A8 (SBU1)
SERVO1_CURRENT: U1.15 (IO3), U11.2 (OUT1)
SERVO1_NRST: R96.2, U9.5 (SC0), U9.6 (SD1), U14.7 (IO1), USB1.B8 (SBU2)
SERVO2_BOOT0: R104.2, U9.8 (SD2), U9.11 (SC3), U14.9 (IO2), USB2.A8 (SBU1)
SERVO2_CURRENT: U1.12 (IO8), U11.8 (OUT2)
SERVO2_NRST: R97.2, U9.9 (SC2), U9.10 (SD3), U14.10 (IO3), USB2.B8 (SBU2)
SERVO3_BOOT0: R105.2, U9.13 (SD4), U9.16 (SC5), U14.11 (IO4), USB3.A8 (SBU1)
SERVO3_CURRENT: U1.9 (IO16), U11.13 (OUT3)
SERVO3_NRST: R98.2, U9.14 (SC4), U9.15 (SD5), U14.12 (IO5), USB3.B8 (SBU2)
SERVO4_BOOT0: R106.2, U13.4 (SD0), U13.7 (SC1), U15.6 (IO0), USB4.A8 (SBU1)
SERVO4_CURRENT: U1.8 (IO15), U11.19 (OUT4)
SERVO4_NRST: R99.2, U13.5 (SC0), U13.6 (SD1), U15.7 (IO1), USB4.B8 (SBU2)
SERVO5_BOOT0: R107.2, U13.8 (SD2), U13.11 (SC3), U15.9 (IO2), USB5.A8 (SBU1)
SERVO5_CURRENT: U1.4 (IO4), U16.2 (OUT1)
SERVO5_NRST: R100.2, U13.9 (SC2), U13.10 (SD3), U15.10 (IO3), USB5.B8 (SBU2)
SERVO6_BOOT0: R108.2, U13.13 (SD4), U13.16 (SC5), U15.11 (IO4), USB6.A8 (SBU1)
SERVO6_CURRENT: U1.7 (IO7), U16.8 (OUT2)
SERVO6_NRST: R101.2, U13.14 (SC4), U13.15 (SD5), U15.12 (IO5), USB6.B8 (SBU2)
STATUS_LED: LED1.2 (A), U1.28 (IO35)
TOUCH_CS: U1.10 (IO17), U35.11 (T_CS)
TOUCH_INT: U1.29 (IO36), U35.14 (T_IRQ)
TX: R33.1, U1.37 (TXD0), U10.25 (RXD)
USBDN1_D+: D1.2 (A1), U24.2 (USBDN1_DP/PRT_DIS_P1), USB1.A6 (DP1), USB1.B6 (DP2)
USBDN1_D-: D1.1 (A1), U24.1 (USBDN1_DM/PRT_DIS_M1), USB1.A7 (DN1), USB1.B7 (DN2)
USBDN2_D+: D2.2 (A1), U24.4 (USBDN2_DP/PRT_DIS_P2), USB2.A6 (DP1), USB2.B6 (DP2)
USBDN2_D-: D2.1 (A1), U24.3 (USBDN2_DM/PRT_DIS_M2), USB2.A7 (DN1), USB2.B7 (DN2)
USBDN3_D+: D5.2 (A1), U24.7 (USBDN3_DP/PRT_DIS_P3), USB3.A6 (DP1), USB3.B6 (DP2)
USBDN3_D-: D5.1 (A1), U24.6 (USBDN3_DM/PRT_DIS_M3), USB3.A7 (DN1), USB3.B7 (DN2)
USBDN4_D+: D9.2 (A1), U24.9 (USBDN4_DP/PRT_DIS_P4), USB4.A6 (DP1), USB4.B6 (DP2)
USBDN4_D-: D9.1 (A1), U24.8 (USBDN4_DM/PRT_DIS_M4), USB4.A7 (DN1), USB4.B7 (DN2)
USBDN5_D+: D10.2 (A1), U24.12 (USBDN5_DP/PRT_DIS_P5), USB5.A6 (DP1), USB5.B6 (DP2)
USBDN5_D-: D10.1 (A1), U24.11 (USBDN5_DM/PRT_DIS_M5), USB5.A7 (DN1), USB5.B7 (DN2)
USBDN6_D+: D11.2 (A1), U24.54 (USBDN6_DP/PRT_DIS_P6), USB6.A6 (DP1), USB6.B6 (DP2)
USBDN6_D-: D11.1 (A1), U24.53 (USBDN6_DM/PRT_DIS_M6), USB6.A7 (DN1), USB6.B7 (DN2)
VANY: C21.2, C22.2, C55.2, C56.2, D12.1 (-), D14.1 (-), U4.3 (VIN), U46.1 (V+), U47.1 (V+)
VBATTERY: D12.2 (+), Q18.5 (D), Q21.5 (D), R8.2 (Shunt-2), R48.2
VBUS: D14.2 (+), Q14.5 (D), R7.2 (Shunt-2), R40.1, R45.2, R68.1, R72.1
VBUS_CURRENT: U1.5 (IO5), U16.19 (OUT4)
VBUS_PINS: R7.1 (Shunt-1), USB0.A4B9 (VBUS), USB0.B4A9 (VBUS)
VBUS_VOLTAGE: C10.2, R45.1, R47.2, U1.38 (IO2)
VCC: Q16.5 (D), Q20.5 (D), Q22.5 (D), R1.2 (Shunt-2), R2.2 (Shunt-2), R3.2 (Shunt-2), R4.2 (Shunt-2), R5.2 (Shunt-2), R6.2 (Shunt-2)
nOCS1: R79.2, U7.4 (/FAULT), U24.28 (OCS1_N)
nOCS2: R80.2, U23.4 (/FAULT), U24.27 (OCS2_N)
nOCS3: R82.2, U24.22 (OCS3_N), U26.4 (/FAULT)
nOCS4: R83.2, U24.21 (OCS4_N), U28.4 (/FAULT)
nOCS5: R84.2, U24.35 (OCS5_N), U30.4 (/FAULT)
nOCS6: R91.2, U24.38 (OCS6_N), U32.4 (/FAULT)

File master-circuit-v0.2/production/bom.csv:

Designator,Footprint,Quantity,Value,LCSC Part #
"C1, C12, C15, C18, C20, C25, C26, C27, C28, C29, C33, C35, C40, C51, C52, C53, C54, C55, C56, C57, C58, C59, C63, C65, C71, C8, C84, C85",C0603,28,1uF,C15849
"C10, C11",C0603,2,1nF,C1588
"C13, C16, C2, C22, C30, C31, C34, C38, C39, C4, C42, C43, C44, C45, C5, C60, C61, C62, C66, C67, C68, C7, C70",C0603,23,100nF,C14663
"C17, C21, C32",C1206,3,10uF,C13585
"C23, C24, C3",C0805,3,22uF,C45783
C6,C0603,1,100pF,C14858
"C64, C69",C0402,2,15pF,C1548
C9,C0603,1,10nF,C57112
"D1, D10, D11, D2, D4, D5, D6, D7, D8, D9",SOT-23-3_L3.0-W1.7-P0.95-LS2.9-BR,10,~,C32677
"D12, D14",SOD-123_L2.7-W1.6-LS3.7-RD-1,2,~,C8598
"FPC1, FPC2, FPC3, FPC4, FPC5, FPC6",FPC-SMD_20P-P0.50_XUNPU_FPC-05F-20PH20,6,~,C2856803
L1,IND-SMD_L4.0-W4.0,1,15uH,C602033
L2,L0805,1,10uH,C1046
LED1,LED0603-RD,1,~,C2286
"Q10, Q9",SOT-23-3_L2.9-W1.3-P1.90-LS2.4-BR,2,~,C2150
"Q12, Q14, Q16, Q18, Q20, Q21, Q22, Q23, Q24, Q25, Q26, Q8",WDFN-5_L3.1-W3.1-P0.65-BL_1,12,~,C7543836
"R1, R2, R3, R4, R5, R6, R7",R2512 Shunt with Kelvin connections,7,5mΩ,C393074
R10,R0603,1,49.9Ω,C23185
"R100, R101, R103, R104, R105, R106, R107, R108, R96, R97, R98, R99",R0402,12,1MΩ,C26083
"R102, R109, R11, R12, R14, R15, R17, R18, R21, R22, R24, R25, R26, R27, R29, R30, R31, R32, R33, R34, R37, R38, R42, R43, R44, R47, R51, R52, R53, R58, R60, R64, R72, R73, R74, R78, R9, R95",R0603,38,10kΩ,C25804
"R13, R28, R46, R59, R65, R71, R76, R85, R86, R87, R88, R89",R0603,12,56kΩ,C23206
R16,R0603,1,120Ω,C22787
"R23, R39",R0603,2,1.5kΩ,C22843
"R35, R55, R61, R66, R67, R70",R0402,6,20kΩ,C25765
R40,R0603,1,20kΩ,C4184
R41,R0603,1,47kΩ,C25819
"R45, R48, R56",R0603,3,100kΩ,C25803
R50,R0603,1,12kΩ,C22790
R62,R0603,1,13kΩ,C22797
R68,R0603,1,1kΩ,C21190
"R77, R81, R90, R92, R93, R94",R0603,6,4.7Ω,C23164
"R79, R80, R82, R83, R84, R91",R0402,6,100kΩ,C25741
R8,R2725 Shunt with Kelvin connections,1,1mΩ,C469381
"SW1, SW2",SW-SMD_4P-L5.1-W5.1-P3.70-LS6.5-TL_H1.5,2,~,C318884
U1,WIRELM-SMD_ESP32-S3-WROOM-1,1,~,C2913202
U10,QFN-28_L5.0-W5.0-P0.50-TL-EP3.3,1,~,C964632
"U11, U16",TSSOP-20_L6.5-W4.4-P0.65-LS6.4-BL,2,~,C2058366
"U13, U9",TSSOP-24_L7.8-W4.4-P0.65-LS6.4-BL,2,~,C130026
"U14, U15",TSSOP-16_L5.0-W4.4-P0.65-LS6.4-BL,2,~,C141380
U17,SOIC-8_L4.9-W3.9-P1.27-LS6.0-BL,1,~,C12084
U18,LGA-16_L3.0-W3.0-P0.50-TL,1,~,C15134
"U23, U26, U28, U30, U32, U7",SOT-23-6_L2.9-W1.6-P0.95-LS2.8-BR,6,~,C55266
U24,QFN-64_L9.0-W9.0-P0.50-BL-EP4.8,1,~,C1521556
U3,SOT-23-5_L3.0-W1.6-P0.95-LS2.8-BL,1,~,C2969807
U4,SOT-23-6_L2.9-W1.6-P0.95-LS2.8-BL,1,~,C191884
"U41, U43, U44, U45, U46, U47, U48, U49",SOIC-8_L4.9-W3.9-P1.27-LS6.0-BL,8,~,C5359091
U42,ESSOP-10_L4.9-W3.9-P1.0-LS6.0-TL-EP,1,~,C970725
"USB0, USB1, USB2, USB3, USB4, USB5, USB6",USB-C-SMD_TYPE-C16PIN,7,~,C393939
X2,CRYSTAL-SMD_4P-L3.2-W2.5-BL,1,24MHz,C15643

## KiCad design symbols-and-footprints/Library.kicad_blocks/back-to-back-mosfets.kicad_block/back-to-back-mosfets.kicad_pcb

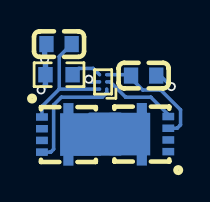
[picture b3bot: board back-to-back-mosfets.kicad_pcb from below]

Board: 4 copper layers, 6 parts (6 on the bottom side), 7 nets.

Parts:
C29, C49: 1uF; C0603
Q5, Q6: WDFN-5_L3.1-W3.1-P0.65-BL_1
R36: 10kΩ; R0603
U12: WLCSP-6_L1.2-W0.8-P0.40-TL

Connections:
/VBUS_PROBE: C29.2, Q5.1 (S), Q5.2 (S), Q5.3 (S), U12.C1 (VOUT)
/back-to-back-mosfets/GATE1x: Q6.4 (G), U12.A1 (VGATE1)
/back-to-back-mosfets/GATE2x: Q5.4 (G), U12.B1 (VGATE2)
/back-to-back-mosfets/Mid-MOSFETSx: Q5.5 (D), Q6.5 (D)
CONNECT_VBUS: R36.2, U12.C2 (VCT)
GND: C29.1, C49.1, R36.1, U12.B2 (GND)
VBUS: C49.2, Q6.1 (S), Q6.2 (S), Q6.3 (S), U12.A2 (VIN)
